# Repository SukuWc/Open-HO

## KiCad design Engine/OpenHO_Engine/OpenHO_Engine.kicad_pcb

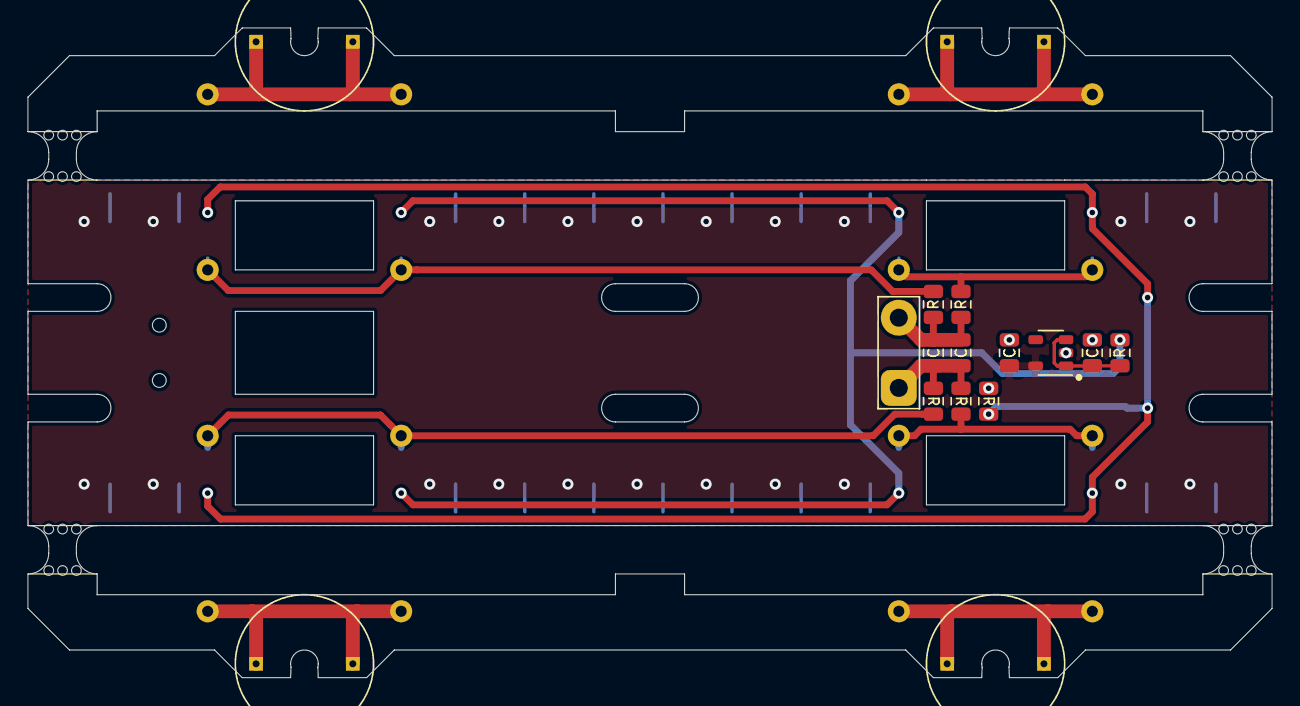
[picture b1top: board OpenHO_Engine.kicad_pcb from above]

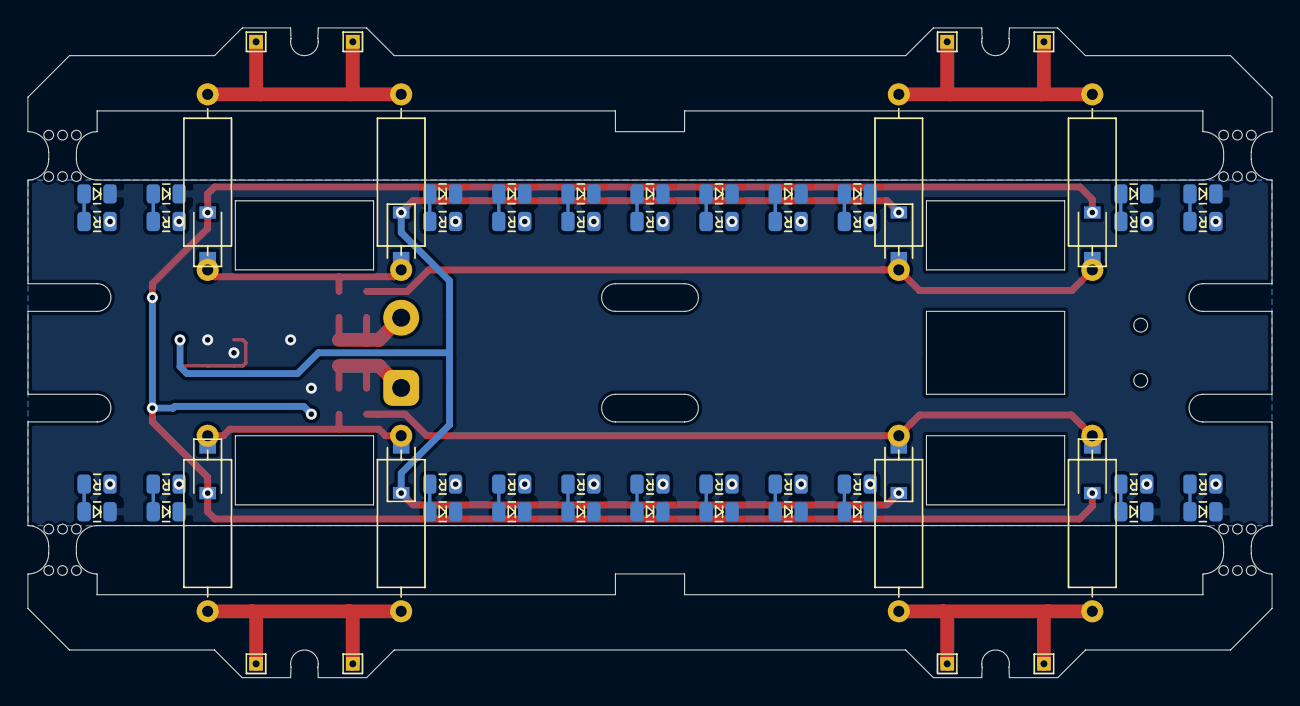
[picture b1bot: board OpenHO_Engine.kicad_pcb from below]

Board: 2 copper layers, 90.0 x 47.0 mm, 84 parts (68 on the bottom side), 37 nets.

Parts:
C1, C2, C3, C4: CAP; CAP_0805
D1, D2, D5, D6, D7, D8, D9, D10, D11, D14, D15, D16, D17, D20, D21, D22, D23, D24, D25, D26, D29, D30: LED; LED_0805
D3, D4, D12, D13, D18, D19, D27, D28: SCHOTTKY; D_SOD-123
H1, H2, H3, H4: MountingHole; PANEL_BREAKOUT-2x3-0.7
J1, J2, J3, J4, J5, J6, J7, J8: Conn_01x01; TestPoint_THTPad_1.0x1.0mm_Drill0.5mm
R1, R2, R3, R6, R7, R8, R9, R10, R11, R12, R13, R15, R17, R18, R19, R20, R21, R22, R25, R26, R27, R28, R29, R30, R31, R33, R35, R36: RES; RES_0805
R4, R5, R14, R16, R23, R24, R32, R34: RES; R_Axial_DIN0309_L9.0mm_D3.2mm_P12.70mm_Horizontal
TP1: TestPoint_2Pole; TestPoint_2Pads_Pitch5.08mm_Drill1.3mm
U1: U_REGULATOR_SOT23-5; SOT-23-5

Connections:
+3V3: C2.1, R1.1, R2.1, R6.1, R7.1, R9.1, R10.1, R11.1, R12.1, R13.1, R17.1, R18.1, R20.1, R21.1, R25.1, R26.1, R27.1, R28.1, R29.1, R30.1, R31.1, R35.1, R36.1, U1.5
+VDC: D3.1, D12.1, D18.1, D27.1, R8.2
+VSW: C3.1, C4.1, R3.1, R15.1, TP1.1
-VDC: D4.2, D13.2, D19.2, D28.2, R19.2
-VSW: C3.2, C4.2, R22.1, R33.1, TP1.2
GND: C1.2, C2.2, D1.1, D2.1, D5.1, D6.1, D7.1, D8.1, D9.1, D10.1, D11.1, D14.1, D15.1, D16.1, D17.1, D20.1, D21.1, D22.1, D23.1, D24.1, D25.1, D26.1, D29.1, D30.1, R19.1, U1.2
unnamed: D1.2, R1.2
unnamed: D2.2, R2.2
unnamed: D3.2, D4.1, R3.2, R4.1, R5.1
unnamed: D5.2, R6.2
unnamed: D6.2, R7.2
unnamed: D7.2, R9.2
unnamed: D8.2, R10.2
unnamed: D9.2, R11.2
unnamed: D10.2, R12.2
unnamed: D11.2, R13.2
unnamed: D12.2, D13.1, R14.1, R15.2, R16.1
unnamed: D14.2, R17.2
unnamed: D15.2, R18.2
unnamed: D16.2, R20.2
unnamed: D17.2, R21.2
unnamed: D18.2, D19.1, R22.2, R23.1, R24.1
unnamed: D20.2, R25.2
unnamed: D21.2, R26.2
unnamed: D22.2, R27.2
unnamed: D23.2, R28.2
unnamed: D24.2, R29.2
unnamed: D25.2, R30.2
unnamed: D26.2, R31.2
unnamed: D27.2, D28.1, R32.1, R33.2, R34.1
unnamed: D29.2, R35.2
unnamed: D30.2, R36.2
unnamed: J1.1, J2.1, R4.2, R5.2
unnamed: J3.1, J4.1, R14.2, R16.2
unnamed: J5.1, J6.1, R23.2, R24.2
unnamed: J7.1, J8.1, R32.2, R34.2
VBUS: C1.1, R8.1, U1.1, U1.3

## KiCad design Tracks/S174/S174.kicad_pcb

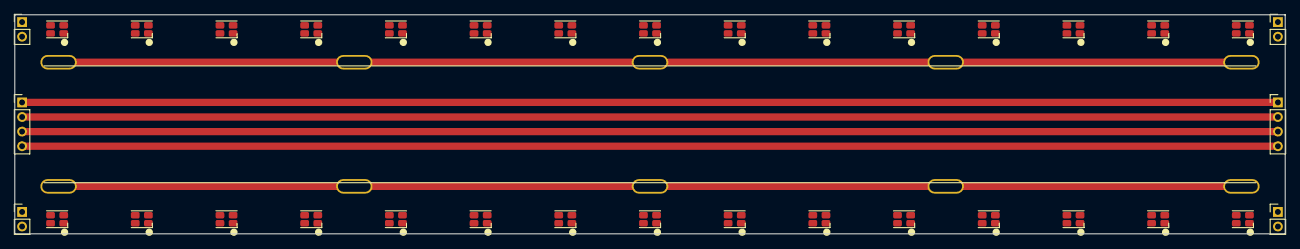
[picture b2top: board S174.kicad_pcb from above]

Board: 2 copper layers, 174.0 x 30.0 mm, 46 parts (0 on the bottom side), 45 nets.

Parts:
D1, D2, D3, D4, D5, D6, D7, D8, D9, D10, D11, D12, D13, D14, D15, D16, D17, D18, D19, D20, D21, D22, D23, D24, D25, D26, D27, D28, D29, D30: UI_WS2812C-2020
J1, J3, J4, J6: Conn_01x02; PinHeader_1x02_P2.00mm_Vertical
J2, J5: Conn_01x04; PinHeader_1x04_P2.00mm_Vertical
TP1, TP2, TP3, TP4, TP5, TP6, TP7, TP8, TP9, TP10: TestPoint; HO_tie

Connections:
+5V: J2.1, J5.1
+VDC: J1.1, J1.2, J4.1, J4.2
+VSW: TP1.1, TP3.1, TP5.1, TP7.1, TP9.1
-VDC: J3.1, J3.2, J6.1, J6.2
-VSW: TP2.1, TP4.1, TP6.1, TP8.1, TP10.1
/LED/DIN: D1.3, D6.3, D11.3, D16.3, D21.3, D26.3
/LED/VDD: D1.4, D2.4, D3.4, D4.4, D5.4
/LED/VSS: D1.2, D2.2, D3.2, D4.2, D5.2
/sheet5E217FEF/VDD: D11.4, D12.4, D13.4, D14.4, D15.4
/sheet5E217FEF/VSS: D11.2, D12.2, D13.2, D14.2, D15.2
/sheet5E217FF0/VDD: D16.4, D17.4, D18.4, D19.4, D20.4
/sheet5E217FF0/VSS: D16.2, D17.2, D18.2, D19.2, D20.2
/sheet5E2189E4/VDD: D21.4, D22.4, D23.4, D24.4, D25.4
/sheet5E2189E4/VSS: D21.2, D22.2, D23.2, D24.2, D25.2
/sheet5E2189E5/VDD: D26.4, D27.4, D28.4, D29.4, D30.4
/sheet5E2189E5/VSS: D26.2, D27.2, D28.2, D29.2, D30.2
/sheet5E217478/VDD: D6.4, D7.4, D8.4, D9.4, D10.4
/sheet5E217478/VSS: D6.2, D7.2, D8.2, D9.2, D10.2
GND: J2.4, J5.4
unnamed: D1.1, D2.3
unnamed: D2.1, D3.3
unnamed: D3.1, D4.3
unnamed: D4.1, D5.3
unnamed: D6.1, D7.3
unnamed: D7.1, D8.3
unnamed: D8.1, D9.3
unnamed: D9.1, D10.3
unnamed: D11.1, D12.3
unnamed: D12.1, D13.3
unnamed: D13.1, D14.3
unnamed: D14.1, D15.3
unnamed: D16.1, D17.3
unnamed: D17.1, D18.3
unnamed: D18.1, D19.3
unnamed: D19.1, D20.3
unnamed: D21.1, D22.3
unnamed: D22.1, D23.3
unnamed: D23.1, D24.3
unnamed: D24.1, D25.3
unnamed: D26.1, D27.3
unnamed: D27.1, D28.3
unnamed: D28.1, D29.3
unnamed: D29.1, D30.3
unnamed: J2.2, J5.2
unnamed: J2.3, J5.3

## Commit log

2020-01-10 SUKU Init commit w/ S174 design file
2020-02-03 SUKU Engine PCB project init
2020-02-07 SUKU engine mock up created
2020-02-10 SUKU protopcb order for Track & Engine
2020-03-16 SUKU Engine Mockup
